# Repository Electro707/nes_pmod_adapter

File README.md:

# NES Controller PMOD Adapter
Design by Jamal Bouajjaj

This adapter board was designed for the University of New Haven's ELEC4475/ELEC6659 System-On-Chip courses, where an NES controller (or clones of it) are connected to a Digilent Spartan development board.

This board adapts an NES controller to a PMOD connector.

The unused pins in the PMOD connection are routed out to a 1 row PMOD connector on the side.

# Diagram Drawing

A diagram of the pinout is available in the folder [diagram](diagram/PinoutDiagram.pdf)

# License
This project, including the board and documentation, are all under a GPLv3 license.

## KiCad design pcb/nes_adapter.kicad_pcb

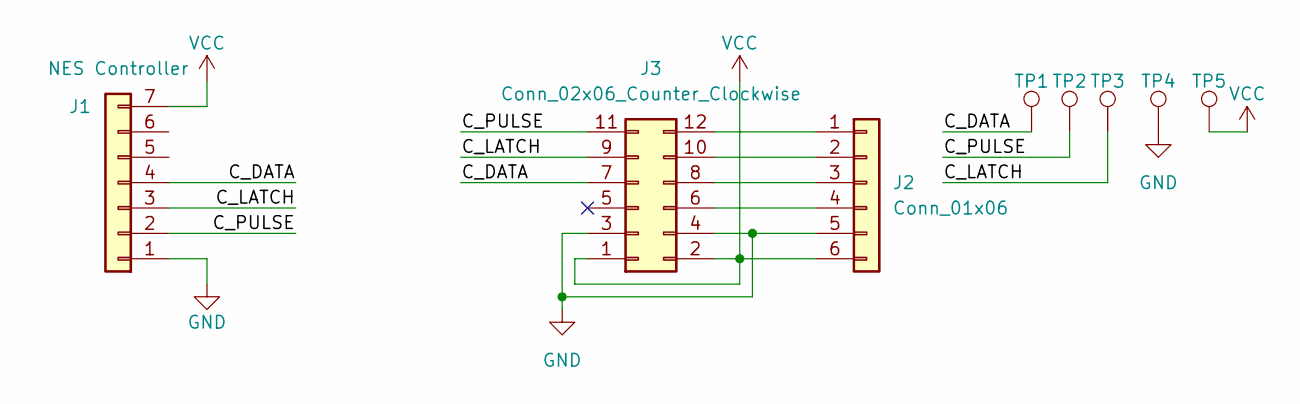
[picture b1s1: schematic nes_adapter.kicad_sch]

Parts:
J1: NES Controller; NES controller port
J2: Conn_01x06; PinHeader_1x06_P2.54mm_Horizontal
J3: Conn_02x06_Counter_Clockwise; PinHeader_2x06_P2.54mm_Horizontal
TP1, TP2, TP3, TP4, TP5: TestPoint; TestPoint_Keystone_5005-5009_Compact

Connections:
/C_DATA: J1.4, J3.7, TP1.1
/C_LATCH: J1.3, J3.9, TP3.1
/C_PULSE: J1.2, J3.11, TP2.1
GND: J1.1, J2.5, J3.3, J3.4, TP4.1
unnamed: J2.1, J3.12
unnamed: J2.2, J3.10
unnamed: J2.3, J3.8
unnamed: J2.4, J3.6
VCC: J1.7, J2.6, J3.1, J3.2, TP5.1

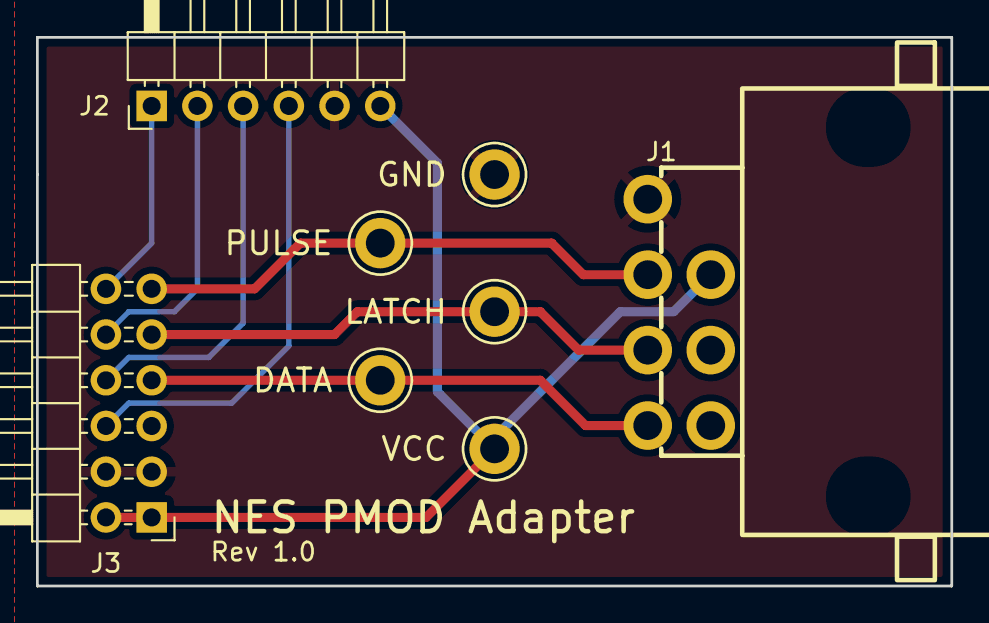
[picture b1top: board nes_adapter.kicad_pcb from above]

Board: 2 copper layers, 50.8 x 30.5 mm, 8 parts (0 on the bottom side), 9 nets.

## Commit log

2024-12-10 Initial Release
